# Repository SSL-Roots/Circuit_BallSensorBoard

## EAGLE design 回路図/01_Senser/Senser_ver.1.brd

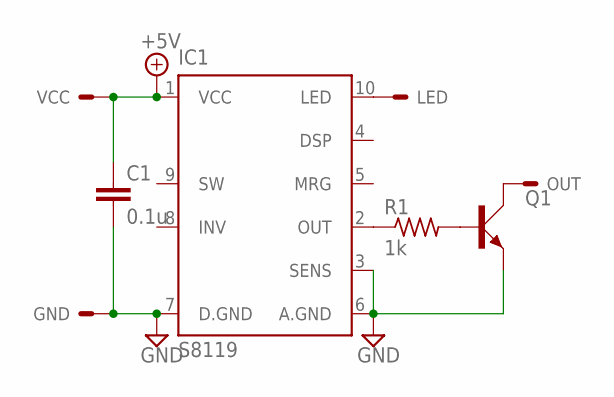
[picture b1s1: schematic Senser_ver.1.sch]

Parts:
C1: 0.1u; C1608
GND: PAD
IC1: S8119
LED: PAD
OUT: PAD
Q1: 2SC2712; SOT23
R1: 1k; R1608
VCC: PAD

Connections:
+5V: C1.1, IC1.1 (VCC), VCC.2
GND: C1.2, GND.2, IC1.3 (SENS), IC1.6 (A.GND), IC1.7 (D.GND), Q1.2 (E)
LED: IC1.10 (LED), LED.2
unnamed: IC1.2 (OUT), R1.1
unnamed: Q1.1 (B), R1.2
unnamed: OUT.2, Q1.3 (C)

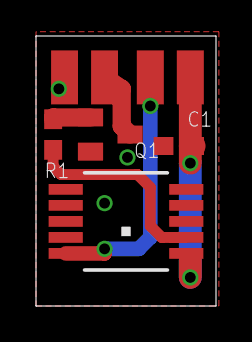
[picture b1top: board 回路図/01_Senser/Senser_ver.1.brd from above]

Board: 2 copper layers, 10.0 x 15.0 mm, 8 parts (0 on the bottom side), 6 nets.

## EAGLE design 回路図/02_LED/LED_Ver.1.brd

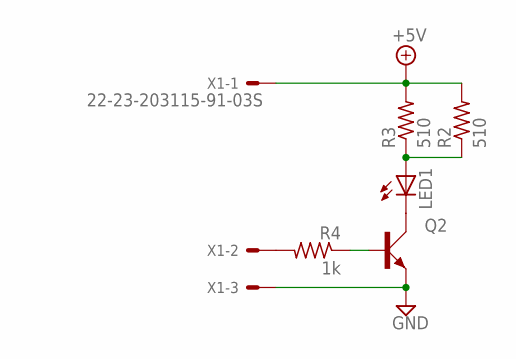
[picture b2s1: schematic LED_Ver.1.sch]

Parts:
LED1: LED3528; KA-3528ASYC
Q2: 2SC2712; SOT23
R2, R3: 510; R1608
R4: 1k; R1608
X1: 22-23-203115-91-03S; 15-91-03S

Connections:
+5V: R2.2, R3.2, X1.1
GND: Q2.2 (E), X1.3
unnamed: LED1.C, Q2.3 (C)
unnamed: LED1.A, R2.1, R3.1
unnamed: R4.2, X1.2
unnamed: Q2.1 (B), R4.1

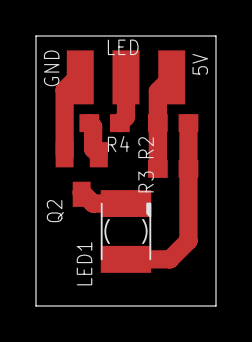
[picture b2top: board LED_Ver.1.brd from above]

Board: 2 copper layers, 10.0 x 15.0 mm, 6 parts (0 on the bottom side), 6 nets.

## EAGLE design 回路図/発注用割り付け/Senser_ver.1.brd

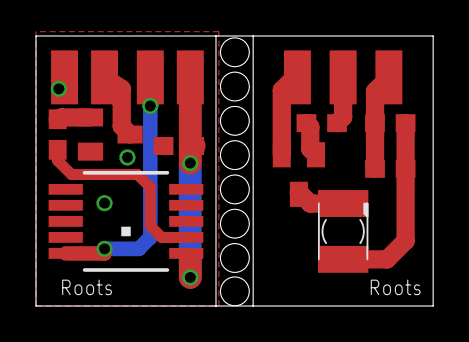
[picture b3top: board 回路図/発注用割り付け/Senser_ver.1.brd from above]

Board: 2 copper layers, 22.1 x 15.0 mm, 14 parts (0 on the bottom side), 12 nets.

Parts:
C1: C1608
GND: PAD
LED: PAD
LED1: KA-3528ASYC
OUT: PAD
Q1, Q2: 2SC1815SOT; SOT23
R1, R2, R3, R4: R1608
U$1: S8119
VCC: PAD
X1: 22-23-203115-91-03S; 15-91-03S

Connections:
+5V: C1.1, U$1.1, VCC.2
+5V1: R2.2, R3.2, X1.1
GND: C1.2, GND.2, Q1.2, U$1.3, U$1.6, U$1.7
GND1: Q2.2, X1.3
LED: LED.2, U$1.10
unnamed: R1.1, U$1.2
unnamed: Q1.1, R1.2
unnamed: OUT.2, Q1.3
unnamed: LED1.C, Q2.3
unnamed: LED1.A, R2.1, R3.1
unnamed: R4.2, X1.2
unnamed: Q2.1, R4.1

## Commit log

2017-08-02 ボールセンサ基板の回路図・運用・作成マニュアル
2020-04-20 Create LICENSE
